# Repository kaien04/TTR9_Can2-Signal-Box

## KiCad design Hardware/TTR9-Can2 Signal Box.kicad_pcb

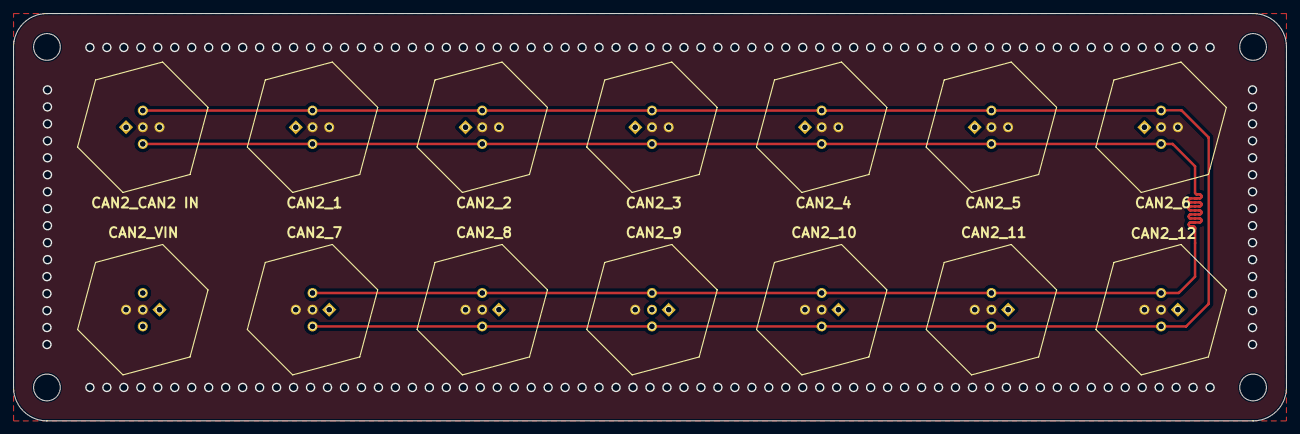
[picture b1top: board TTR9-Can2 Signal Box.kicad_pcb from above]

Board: 2 copper layers, 190.5 x 61.0 mm, 18 parts (0 on the bottom side), 4 nets.

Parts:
H1, H2, H3, H4: MountingHole; MountingHole_4mm
J1: CAN2_IN; 643260100405
J2: CAN2_1; 643260100405
J3: CAN2_2; 643260100405
J4: CAN2_3; 643260100405
J5: CAN2_4; 643260100405
J6: CAN2_5; 643260100405
J7: CAN2_6; 643260100405
J8: CAN2_7; 643260100405
J9: CAN2_8; 643260100405
J10: CAN2_9; 643260100405
J11: CAN2_10; 643260100405
J12: CAN2_11; 643260100405
J13: CAN2_12; 643260100405
J14: CAN2_VIN; 643260100405

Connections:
+12V: J2.1, J3.1, J4.1, J5.1, J6.1, J7.1, J8.1, J9.1, J10.1, J11.1, J12.1, J13.1, J14.1
/CAN2.+: J1.2, J2.2, J3.2, J4.2, J5.2, J6.2, J7.2, J8.2, J9.2, J10.2, J11.2, J12.2, J13.2
/CAN2.-: J1.4, J2.4, J3.4, J4.4, J5.4, J6.4, J7.4, J8.4, J9.4, J10.4, J11.4, J12.4, J13.4
GND: J1.3, J1.5, J2.3, J2.5, J3.3, J3.5, J4.3, J4.5, J5.3, J5.5, J6.3, J6.5, J7.3, J7.5, J8.3, J8.5, J9.3, J9.5, J10.3, J11.3, J11.5, J12.3, J12.5, J13.3, J13.5, J14.3, J14.5

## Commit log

2026-05-11 Initial commit: TTR9_Can2 Signal Box v1
2026-05-12 change Can2 wire from 0.2mm to 0.381mm
